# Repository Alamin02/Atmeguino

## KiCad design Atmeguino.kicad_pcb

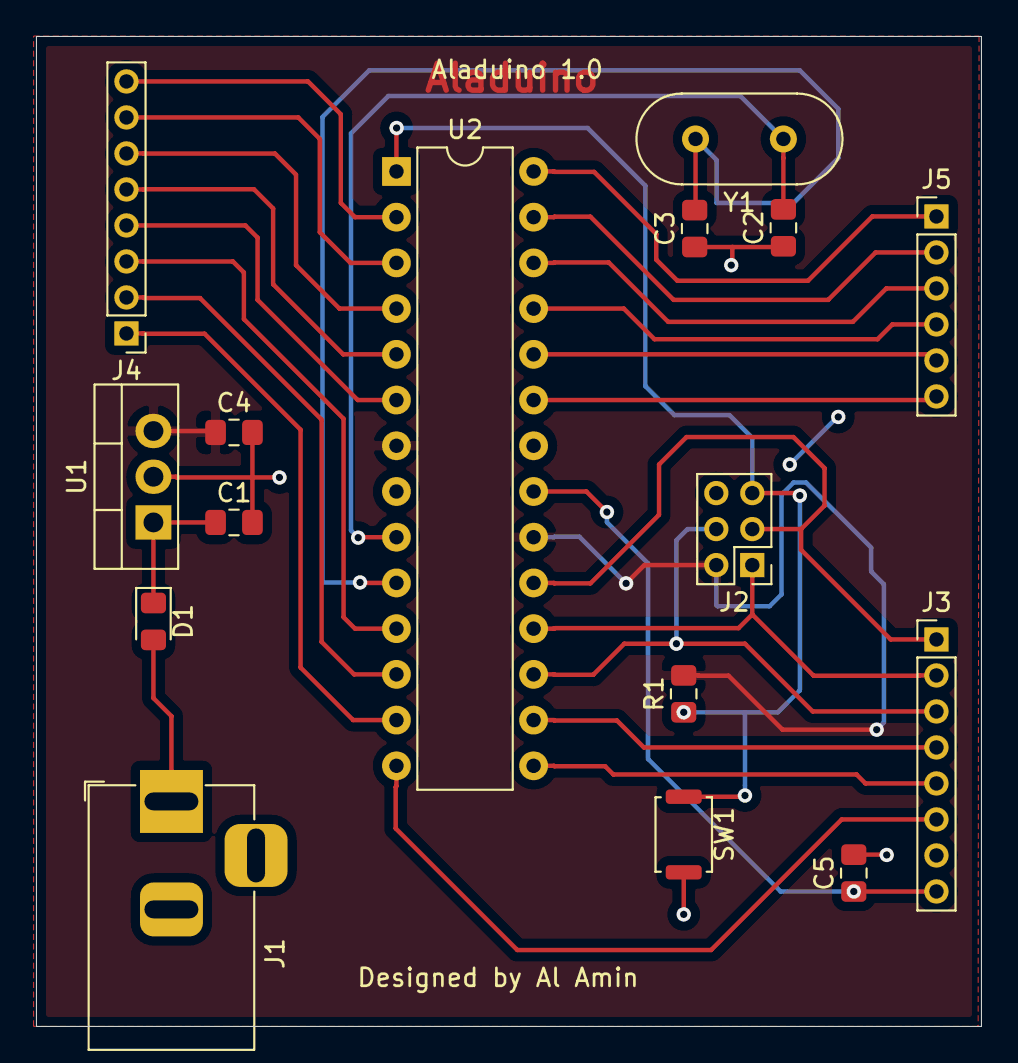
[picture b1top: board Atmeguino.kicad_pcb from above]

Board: 2 copper layers, 52.5 x 55.0 mm, 16 parts (0 on the bottom side), 28 nets.

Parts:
C1, C2, C3, C4, C5: C; C_0805_2012Metric_Pad1.15x1.40mm_HandSolder
D1: D; D_0805_2012Metric_Pad1.15x1.40mm_HandSolder
J1: Barrel_Jack; BarrelJack_Horizontal
J2: Conn_02x03_Odd_Even; PinHeader_2x03_P2.00mm_Vertical
J3, J4: Conn_01x08_Male; PinHeader_1x08_P2.00mm_Vertical
J5: Conn_01x06_Male; PinHeader_1x06_P2.00mm_Vertical
R1: R; R_0805_2012Metric_Pad1.15x1.40mm_HandSolder
SW1: SW_Push; SW_Push_SPST_NO_Alps_SKRK
U1: L7805; TO-220-3_Vertical
U2: ATmega8L-8PU; DIP-28_W7.62mm
Y1: Crystal; Crystal_HC49-4H_Vertical

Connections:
/VCC: C4.1, J2.2, R1.2, U1.3, U2.7, U2.20
GND: C1.2, C2.1, C3.1, C4.2, C5.2, J1.2, J2.6, J3.7, SW1.2, U1.2, U2.8, U2.22
unnamed: C1.1, D1.1, U1.1
unnamed: C2.2, U2.9, Y1.1
unnamed: C3.2, U2.10, Y1.2
unnamed: C5.1, J3.8, U2.21
unnamed: D1.2, J1.1
unnamed: J2.1, J3.2, U2.18
unnamed: J2.3, J3.1, U2.19
unnamed: J2.4, J3.3, U2.17
unnamed: J2.5, R1.1, SW1.1, U2.1
unnamed: J3.4, U2.16
unnamed: J3.5, U2.15
unnamed: J3.6, U2.14
unnamed: J4.1, U2.13
unnamed: J4.2, U2.12
unnamed: J4.3, U2.11
unnamed: J4.4, U2.6
unnamed: J4.5, U2.5
unnamed: J4.6, U2.4
unnamed: J4.7, U2.3
unnamed: J4.8, U2.2
unnamed: J5.1, U2.28
unnamed: J5.2, U2.27
unnamed: J5.3, U2.26
unnamed: J5.4, U2.25
unnamed: J5.5, U2.24
unnamed: J5.6, U2.23
